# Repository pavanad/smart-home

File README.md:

# Smart Home

My personal smart home project using open source technologies

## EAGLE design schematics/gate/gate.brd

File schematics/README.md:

# Device schematics

Custom PCBs for devices

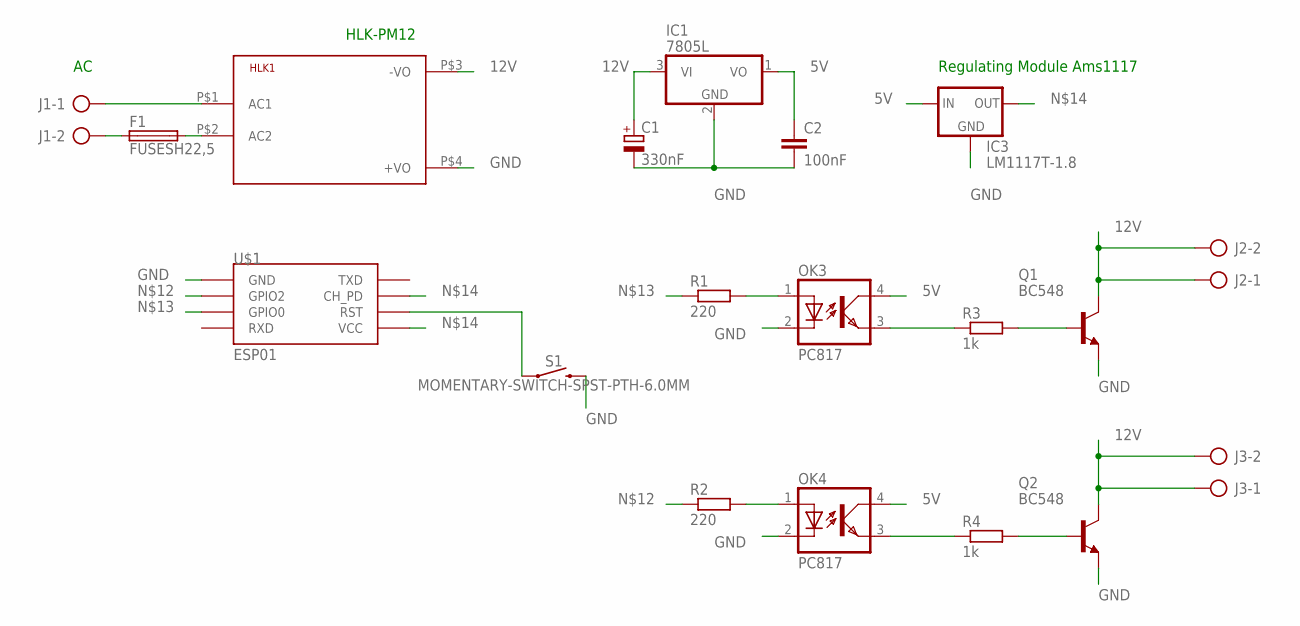
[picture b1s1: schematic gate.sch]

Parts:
C1: 330nF; E2,5-6
C2: 100nF; C050-024X044
F1: FUSESH22,5; SH22,5
HLK1: HLK-PM013W; HLK-PM01
IC1: 7805L; TO92
IC3: LM1117T-1.8; TO220
J1, J2, J3: AK500/2-H
OK3, OK4: PC817; DIL04
Q1, Q2: BC548; TO92-EBC
R1, R2: 220; 0204/7
R3, R4: 1k; 0204/7
S1: MOMENTARY-SWITCH-SPST-PTH-6.0MM; TACTILE_SWITCH_PTH_6.0MM
U$1: ESP01

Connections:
5V: C2.1, IC1.1 (VO), IC3.3 (IN), OK3.4 (COL), OK4.4 (COL)
12V: C1.+, HLK1.P$3 (-VO), IC1.3 (VI), J2.1, J2.2, J3.1, J3.2, Q1.C, Q2.C
GND: C1.-, C2.2, HLK1.P$4 (+VO), IC1.2 (GND), IC3.1 (GND), OK3.2 (C), OK4.2 (C), Q1.E, Q2.E, S1.3 (2), U$1.GND
unnamed: HLK1.P$1 (AC1), J1.1
unnamed: F1.1, J1.2
unnamed: F1.2, HLK1.P$2 (AC2)
unnamed: OK3.1 (A), R1.2
unnamed: OK4.1 (A), R2.2
unnamed: Q1.B, R3.2
unnamed: Q2.B, R4.2
unnamed: OK4.3 (EMIT), R4.1
unnamed: OK3.3 (EMIT), R3.1
unnamed: S1.1, U$1.RST
unnamed: R2.1, U$1.GPIO2
unnamed: R1.1, U$1.GPIO0
unnamed: IC3.2 (OUT), U$1.CH_PD, U$1.VCC

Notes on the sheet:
HLK-PM12
Regulating Module Ams1117

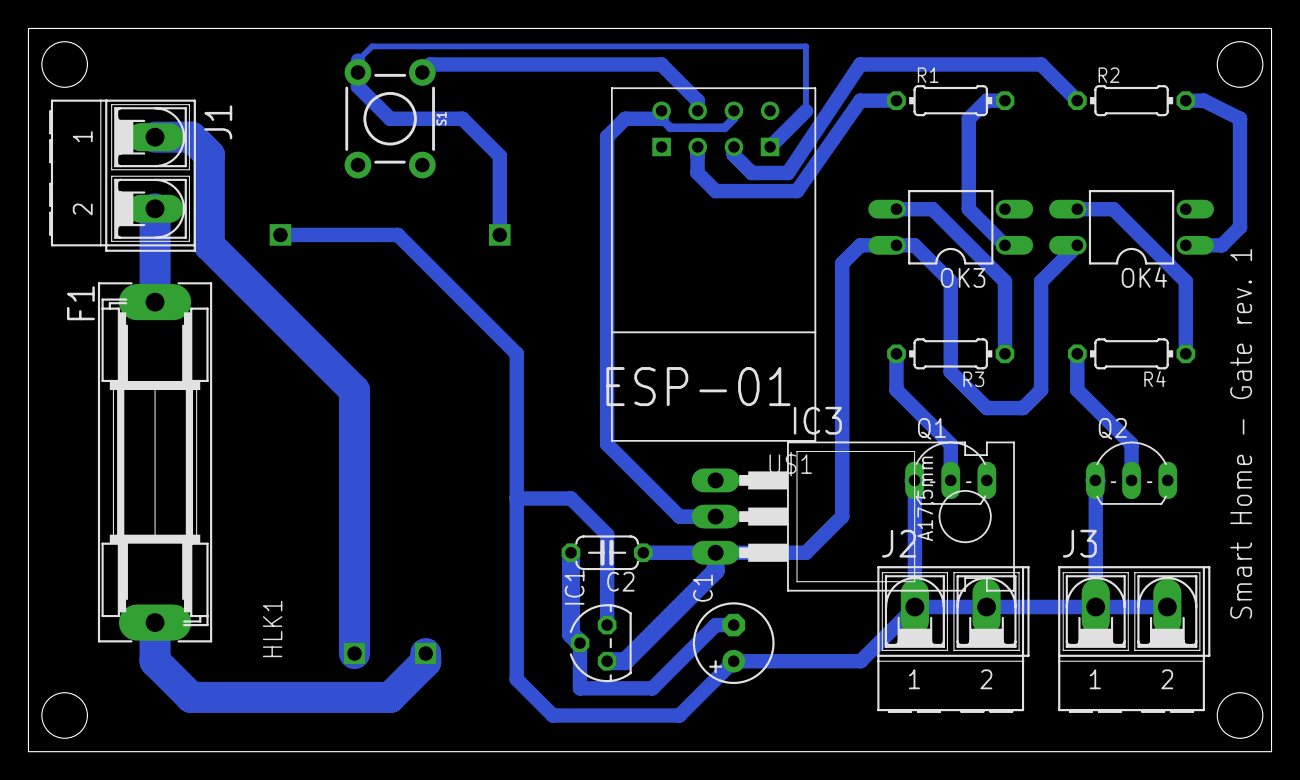
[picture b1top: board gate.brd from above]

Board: 2 copper layers, 87.3 x 50.8 mm, 19 parts (0 on the bottom side), 16 nets.

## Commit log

2018-07-05 adding schematic of the gate circuit
2018-07-05 adding list of components
2018-07-06 change package 7805 and change ground plane
2018-07-27 adding gate schematic in png
2018-09-21 fix bug in circuit
2018-10-06 add image of the gate board
2018-10-06 remove test files
2019-12-27 first commit of the gate firmware
2019-12-27 adding readme files
2019-12-29 firmware of the social gate
2019-12-29 update readmes
2019-12-31 change value topic for MQTT lock
2020-01-24 home assistant configuration files and some information

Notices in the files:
parts and their libraries:
SparkFun-Switches: Licensing: Creative Commons ShareAlike 4.0 International - https://creativecommons.org/licenses/by-sa/4.0
